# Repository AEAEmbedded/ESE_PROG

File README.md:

# ESE_PROG - Programming 5 / 6 (2026-2027)

Course repository for **Programming 5 (Prog 5)** and **Programming 6 (Prog 6)** of the
Embedded Systems Engineering track, Software Engineering, HAN University of Applied Sciences.

| Course | Period | When | Folder |
| --- | --- | --- | --- |
| **Prog 5** | Period 1 | September - October 2026 | [`Prog5/`](Prog5/) - lectures, labs, assignments, example code |
| **Prog 6** | Period 2 | November 2026 - January 2027 | [`Prog6/`](Prog6/) - workshops, Hackathon, Challenge, rubrics |

## Welcome to Prog 5

Prog 5 and Prog 6 are the final lap of the programming courses in your ESE journey. Together they
work towards one overall goal: **becoming a professional embedded software and systems developer**.

Prog 5 (period 1) is about object-oriented C++ on microcontrollers (Arduino / SAMD21) and on the
Raspberry Pi: writing sensor libraries, designing them with UML, connecting them to the outside
world (I2C, MQTT) and testing them. Prog 6 (period 2) builds on that with software-engineering
practice - build systems, unit testing, clean code and design patterns - and applies it in the
Hackathon and the Challenge project.

### Why everything is done with Git

All work in Prog 5 and 6 is done with **Git**, because it is the only way to reach our learning
goals. Git:

* lets several developers work on the same project at the same time;
* keeps a complete history of every change to the code;
* makes it easy to revert a change or recover an earlier version;
* helps you resolve conflicts between contributions efficiently.

More importantly, it takes you out of an artificial learning environment and into the professional
field: the companies where you will do your internship and, later, land a job use exactly these
tools. Being fluent in them is part of being a professional - see
[Coder vs Developer vs Software Engineer: what's the difference?](https://youtu.be/fcjBfSiyI0k)

### Handing in your work

Put your assignments in a (private) Git repository and add your lecturer as a collaborator
(GitHub username **jakorten**). Commit as you go - a
repository with a real history of small, meaningful commits is part of what is assessed.

## Prog 5 schedule and deadlines (period 1, 2026-2027)

The course starts on **Thursday 3 September 2026** and runs for seven weeks. Every week combines
one design principle, a C++ topic and a UML topic, and every Friday there is a lab. The first two
labs are Git and Requirements; from week 3 onwards the Friday lab is the next step of **one sensor
library** that grows week by week (the BME280 is the concrete sensor we use; another I2C sensor
works just as well). The same seven-step plan is on the schedule slide of every lecture deck.

| Week | Lecture (Thu) | Design principle | C++ | UML | Slides | Lab (Fri) |
| :-: | --- | --- | --- | --- | --- | --- |
| 1 | 3 Sep 2026 | Single Responsibility | Scope, namespaces, string | Use cases / class diagram | [0. Course introduction](Prog5/Keynotes/), [1. Introduction](Prog5/Keynotes/) | Fri 4 Sep: [Git workshop 1](Prog5/Workshops/Git/Workshop1_Basics.md) - the basics (clone, add, commit, push, .gitignore, handing in) |
| 2 | 10 Sep 2026 | Open-Closed Principle | Constructors, iterators, lambdas | Inheritance / generalization | [2. Constructors and more](Prog5/Keynotes/) | Fri 11 Sep: Requirements (SMART, FURPS+, MoSCoW, use cases) |
| 3 | 17 Sep 2026 | Liskov Substitution Principle | Lists, inline functions, default params | Activity diagrams | [3. Lists, inline functions and default params](Prog5/Keynotes/) | Fri 18 Sep: sensor library 1 - core, `Bus`, Arduino |
| 4 | 24 Sep 2026 | Interface Segregation Principle | Interfaces and abstract classes | Dependencies | [4. Interfaces and abstract classes](Prog5/Keynotes/) | Fri 25 Sep: sensor library 2 - Raspberry Pi, `Bus` / `Clock` split |
| 5 | 1 Oct 2026 | Dependency Inversion Principle | Threads, callbacks | Sequence diagrams | [5. Threading and callbacks](Prog5/Keynotes/) | Fri 2 Oct: sensor library 3 - sampler thread, callback, MQTT |
| 6 | 8 Oct 2026 | Coupling and cohesion | Polymorphism | Composition, packages | [6. Polymorphism](Prog5/Keynotes/) | Fri 9 Oct: sensor library 4 - polymorphism, UML design |
| 7 | 15 Oct 2026 | Embedded SOLID | Lifecycle: constructors, destructors, const | - | [7. Lifecycle](Prog5/Keynotes/) | Fri 16 Oct: sensor library 5 - RAII, host unit tests, refactor |

Each assignment is introduced in the lecture of the week listed below and is due **one week
later, on the Thursday of the following week**. Full hand-outs: [`Prog5/Assignments/`](Prog5/Assignments/).

| Week | Lecture | Assignment | Deadline |
| :-: | --- | --- | --- |
| 1 | Thu 3 Sep 2026 | **1.** Make a basic stepper motor library and hand it in via your Git repository. | Thu 10 Sep 2026 |
| 2 | Thu 10 Sep 2026 | **2.** Create a UML use-case diagram with description for a sensor application (e.g. KNMI / weather station). | Thu 17 Sep 2026 |
| 3 | Thu 17 Sep 2026 | **3.** [Sensor library, core + Arduino](Prog5/Assignments/week3/bme280_arduino_library.md): Bosch driver wrapped in a class, `Bus` interface, `ArduinoI2cBus`, example sketch. Tag `v0.3-arduino`. | Thu 24 Sep 2026 |
| 4 | Thu 24 Sep 2026 | **4.** [Same library on the Raspberry Pi](Prog5/Assignments/week4/bme280_raspberry_pi.md): CMake build, `LinuxI2cBus`, `Bus` / `Clock` split (ISP), dependency diagram. Tag `v0.4-pi`. | Thu 1 Oct 2026 |
| 5 | Thu 1 Oct 2026 | **5.** [Sampling thread, callback, MQTT](Prog5/Assignments/week5/bme280_mqtt.md): `Sampler`, `Publisher` / `MqttPublisher`, `EnvironmentSensor` + `FakeSensor`, sequence diagram sketch. Tag `v0.5-mqtt`. | Thu 8 Oct 2026 |
| 6 | Thu 8 Oct 2026 | **6.** [Design on paper](Prog5/Assignments/week6/bme280_uml_design.md): class, package and sequence diagrams of the library; `vector<EnvironmentSensor*>` with a second sensor. Tag `v0.6-design`. | Thu 15 Oct 2026 |
| 7 | Thu 15 Oct 2026 | **7.** [Unit tests on the host](Prog5/Assignments/week7/bme280_tests_and_refactor.md) with the `MockBus` (no mocking framework yet). <br> **8.** Review the library against DRY, KISS, SOLID, coupling / cohesion and the lifecycle checklist; add a second sensor and move the shared abstractions (`Bus`, `Clock`, `EnvironmentSensor`) into their own package; refactor and report. Tag `v1.0`. | Thu 22 Oct 2026 |

**Resit:** assignments that were not handed in on time, or that did not pass, can be (re)submitted
until the resit deadline of **Thursday 29 October 2026**.

Assignments 3-8 all build on the same sensor library (the Friday labs are its steps), so keep it in one repository and let its
history show how it grows: from a first Arduino version to a tested, refactored Pi library that
publishes over MQTT. Starter code per week is in [`Prog5/Code/`](Prog5/Code/) (`week2`: the
wrapper library, `week4`: Linux I2C bus, `week5`: sampler + MQTT).

## Learning outcomes

The learning outcomes below follow the HAN engineering competencies used in the rubrics
(*Analyze - Design - Manage - Control - Realize - Professionalize*). Prog 5 lays the foundation;
Prog 6 raises every outcome to a professional level and assesses it in the Hackathon and the
Challenge.

### Prog 5 - after period 1 you can

| # | Learning outcome | Competency |
| :-: | --- | --- |
| P5.1 | **Analyse** a realistic problem into user stories and SMART requirements, categorised with FURPS+ and prioritised with MoSCoW. | Analyze |
| P5.2 | **Design** software with UML: a use-case diagram with descriptions, a class diagram and a sequence diagram (and a state diagram where behaviour asks for it). | Design |
| P5.3 | **Implement** object-oriented C++ on embedded targets (Arduino / SAMD21 and Raspberry Pi): classes and encapsulation, constructors/destructors and object lifecycle, inheritance, abstract classes and interfaces, polymorphism, smart pointers, lambdas and callbacks, basic concurrency. | Realize |
| P5.4 | **Build reusable sensor libraries**: an Arduino library for an (I2C) sensor, a C++ library for an I2C sensor on the Raspberry Pi, and connect it to an MQTT broker. | Realize |
| P5.5 | **Apply DRY, KISS, SOLID and loose coupling / strong cohesion**, recognise where your own code violates them, refactor it and explain what improved. | Realize |
| P5.6 | **Test** a library with basic unit tests in C++. | Control |
| P5.7 | **Use Git professionally** for all your work: meaningful commits, branches, pull requests and a readable history, in a repository you share with your lecturer. | Manage |

### Prog 6 - after period 2 you can

| # | Learning outcome | Competency |
| :-: | --- | --- |
| P6.1 | **Set up and maintain a CMake build** for a C/C++ project with its own libraries and externally fetched test dependencies, and explain why build systems exist. | Realize |
| P6.2 | **Unit test at a professional level** with CppUTest, including test doubles and mocks for hardware dependencies, and position tests in the testing pyramid. | Control |
| P6.3 | **Write clean, well-commented, maintainable code**: recognise code smells, apply MISRA C++:2023 guidelines and use static-analysis tooling to check your own code. | Realize |
| P6.4 | **Apply embedded design patterns and architecture** (state, observer, hardware proxy, cyclic executive, debouncing, fixed-point arithmetic, humble object) with awareness of their run-time and memory overhead. | Design |
| P6.5 | **Realise a working proof-of-concept** for a healthcare case (Wilhelmina Children's Hospital, WKZ) - in a team under time pressure in the Hackathon and in the longer Challenge project - from analysis and SOLID design, through technical designs (class, sequence, state), to a tested implementation. | Analyze / Design / Realize |
| P6.6 | **Manage code as a team** in Git with commits, pull requests, blame and code reviews throughout the project. | Manage |
| P6.7 | **Reflect and advise**: give substantiated advice based on your analysis and proof-of-concept and present it convincingly (presentation, report or video), communicating professionally with the team, lecturers and domain experts. | Professionalize |

Assessment: Prog 5 by the weekly assignments (see schedule below); Prog 6 with the
[Hackathon and Prog 6 rubrics](Prog6/Rubrics/).

## Repository layout

| Folder | Contents |
| --- | --- |
| [`Prog5/Keynotes/`](Prog5/Keynotes/) | Lecture slides (PDF): course introduction and lectures 1-7. |
| [`Prog5/Labs/`](Prog5/Labs/) | Lab hand-outs (Lab 2: Arduino basics with OOP / SOLID; Lab 3: I2C sensor library). |
| [`Prog5/Assignments/`](Prog5/Assignments/) | Assignment hand-outs per week; from week 3 on all steps of the one sensor library (BME280 as the worked example). |
| [`Prog5/Code/week1/`](Prog5/Code/week1/) | Week 1 example code: stepper motor examples, `SimpleStepper` library, TB6600 test. |
| [`Prog5/Code/week2/`](Prog5/Code/week2/) | BME280 starter library: `Bus` interface, wrapper around the vendored Bosch BME280 SensorAPI, `MockBus` + doctest. |
| [`Prog5/Code/week4/`](Prog5/Code/week4/) | `rpi_platform`: `LinuxI2cBus` on `/dev/i2c-1` and a smoke test, CMake build of core + platform. |
| [`Prog5/Code/week5/`](Prog5/Code/week5/) | `mqtt_station`: `EnvironmentSensor`, `Sampler` (thread + callback), `Publisher` / `MqttPublisher` (libmosquitto), composition root. |
| [`Prog5/Code/Examples/`](Prog5/Code/Examples/) | Demo code used in the lectures and labs (abstract interfaces, object lifecycle, ToF sensor library, SOLID terminal, I2C scanner). |
| [`Prog5/Workshops/Git/`](Prog5/Workshops/Git/) | Git workshops 1 (the basics) and 2 (working together), with an interactive version. |
| [`Prog5/Demos/`](Prog5/Demos/) | Hand-outs: Git manual, CMake basics, interfaces demo. |
| [`Prog6/Workshops/`](Prog6/Workshops/) | Workshops: CMake, Unit Testing (CppUTest), Commenting, Clean Code / MISRA C++, Design Patterns & Architecture. |
| [`Prog6/Hackathon/`](Prog6/Hackathon/) | Hackathon material: the VitalSignsBox modules (ECG lead detection, SpO2 detection, temperature sensors) with firmware, API descriptions and hardware files. |
| [`Prog6/Challenge/`](Prog6/Challenge/) | Challenge project: assignment document and hardware design files (SensorHub, ActuatorHub, sim modules, adapters). |
| [`Prog6/Rubrics/`](Prog6/Rubrics/) | Assessment rubrics 2026-2027 (Prog 6 v1.5, Hackathon v1.4; Markdown source + PDF) and previous editions. |
| [`Resources/`](Resources/) | Background reading, e.g. choosing a development method. |

## How to use

1. Clone the repository: `git clone https://github.com/AEAEmbedded/ESE_PROG`
2. Arduino sketches (`*.ino`): open the sketch folder in the Arduino IDE and upload to your board.
3. CMake projects (workshops): configure out-of-source, e.g.
   ```bash
   cmake -S Prog6/Workshops/UnitTesting/Source/TemperatureTestFinished -B build
   cmake --build build
   ctest --test-dir build
   ```
   Build directories are ignored by git - do not commit them.
4. Refer to the keynotes, labs and workshop READMEs for instructions.

## Related repositories

* **[PiTest](https://github.com/jakorten/PiTest)** - Raspberry Pi 4 to SensorHub (SAMD21) I2C communication test (Python for the Pi, C++ Arduino sketches for the SAMD21).

## Disclaimer

This repository is for educational purposes. The code may be incomplete or contain errors. Use at your own risk.

## Contact

Johan Korten - johan.korten@han.nl

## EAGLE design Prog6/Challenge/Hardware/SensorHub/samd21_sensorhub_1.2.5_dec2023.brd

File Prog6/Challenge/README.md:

# Challenge

This folder contains resources for the Prog6 Challenge project.

## Repositories

- **[PiTest](https://github.com/jakorten/PiTest)** - Raspberry Pi 4 to SensorHub (SAMD21) I2C communication test
 - Python I2C test script for Pi
 - C++ Arduino sketch for SAMD21
 - Pinout documentation

## Contents

- **HAN_Challenge_Prog_6_2025.pdf** - Challenge assignment document (2025 edition; to be updated for 2026-2027)
- **Hardware/** - Hardware design files and schematics

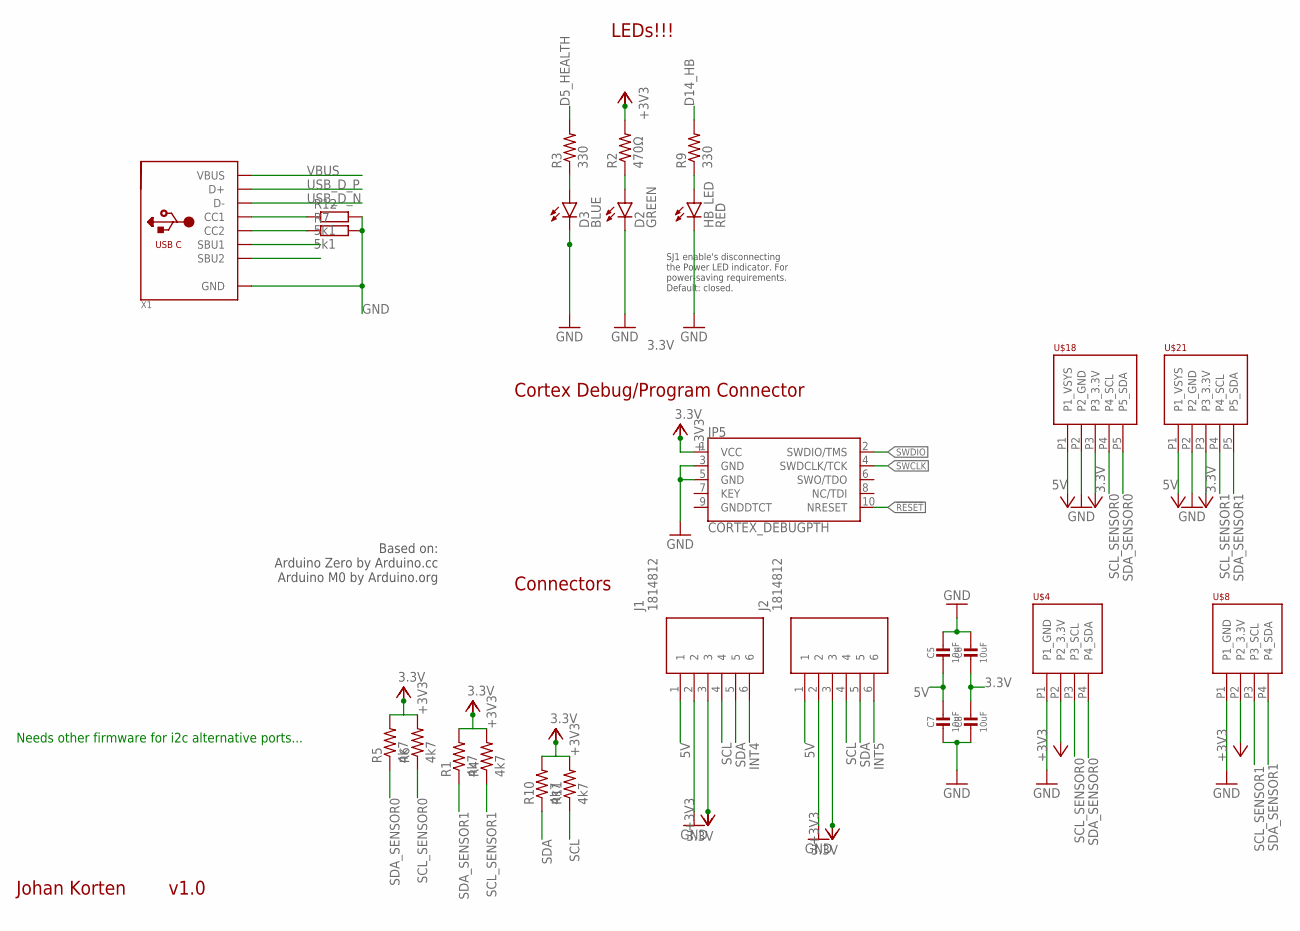
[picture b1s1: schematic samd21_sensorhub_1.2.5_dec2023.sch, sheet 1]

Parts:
C5, C6, C7, C8: 10uF; 0805-NO
D2: GREEN; LED-0603
D3: BLUE; LED-0603
HB_LED: RED; LED-0603
J1, J2: 1814812
JP5: CORTEX_DEBUGPTH; 2X5-PTH-1.27MM
R1, R4, R5, R6, R10, R11: 4k7; 0603-RES
R2: 470Ω; 0603-RES
R3, R9: 330; 0603-RES
R7, R12: 5k1; R0603
U$4, U$8: PHOENIX_PTSM_M4_THANGLE; PTSM_M4_TH
U$18, U$21: PHOENIX_PTSM_M5_TH_I2C++; PTSM_M5_THRHOLE
X1: USB_C; USB_C_CUSB31-CFM2AX-01-X

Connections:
3.3V: C6.2, C8.1, J1.3, J2.3, JP5.1 (VCC), R1.2, R2.2, R4.2, R5.2, R6.2, R10.2, R11.2, U$4.P2 (P2_3.3V), U$8.P2 (P2_3.3V), U$18.P3 (P3_3.3V), U$21.P3 (P3_3.3V); also elsewhere on the board
5V: C5.2, C7.1, J1.1, J2.1, U$18.P1 (P1_VSYS), U$21.P1 (P1_VSYS); also elsewhere on the board
!RESET: JP5.10 (NRESET); also elsewhere on the board
D5_HEALTH: R3.2; also elsewhere on the board
D5_HEALTH_LED: D3.A, R3.1
D14_HB: R9.2; also elsewhere on the board
D14_HB_LED: HB_LED.A, R9.1
GND: C5.1, C6.1, C7.2, C8.2, D2.C, D3.C, HB_LED.C, J1.2, J2.2, JP5.3 (GND), JP5.5 (GND), R7.2, R12.2, U$4.P1 (P1_GND), U$8.P1 (P1_GND), U$18.P2 (P2_GND), U$21.P2 (P2_GND), X1.A1B12 (GND), X1.B1A12 (GND); also elsewhere on the board
INT4: J1.6; also elsewhere on the board
INT5: J2.6; also elsewhere on the board
unnamed: R12.1, X1.A5 (CC1)
unnamed: R7.1, X1.B5 (CC2)
unnamed: D2.A, R2.1
SCL: J1.4, J2.4, R11.1; also elsewhere on the board
SCL_SENSOR0: R6.1, U$4.P3 (P3_SCL), U$18.P4 (P4_SCL); also elsewhere on the board
SCL_SENSOR1: R4.1, U$8.P3 (P3_SCL), U$21.P4 (P4_SCL); also elsewhere on the board
SDA: J1.5, J2.5, R10.1; also elsewhere on the board
SDA_SENSOR0: R5.1, U$4.P4 (P4_SDA), U$18.P5 (P5_SDA); also elsewhere on the board
SDA_SENSOR1: R1.1, U$8.P4 (P4_SDA), U$21.P5 (P5_SDA); also elsewhere on the board
SWCLK: JP5.4 (SWDCLK/TCK); also elsewhere on the board
SWDIO: JP5.2 (SWDIO/TMS); also elsewhere on the board
USB_D_N: X1.A7 (D-), X1.B7 (D-); also elsewhere on the board
USB_D_P: X1.A6 (D+), X1.B6 (D+); also elsewhere on the board
VBUS: X1.A4B9 (VBUS), X1.B4A9 (VBUS); also elsewhere on the board

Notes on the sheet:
LEDs!!!
Cortex Debug/Program Connector
Connectors
Johan Korten
v1.0
SJ1 enable's disconnecting the Power LED indicator. For power-saving requirements. Default: closed.
Based on: Arduino Zero by Arduino.cc Arduino M0 by Arduino.org
Needs other firmware for i2c alternative ports...

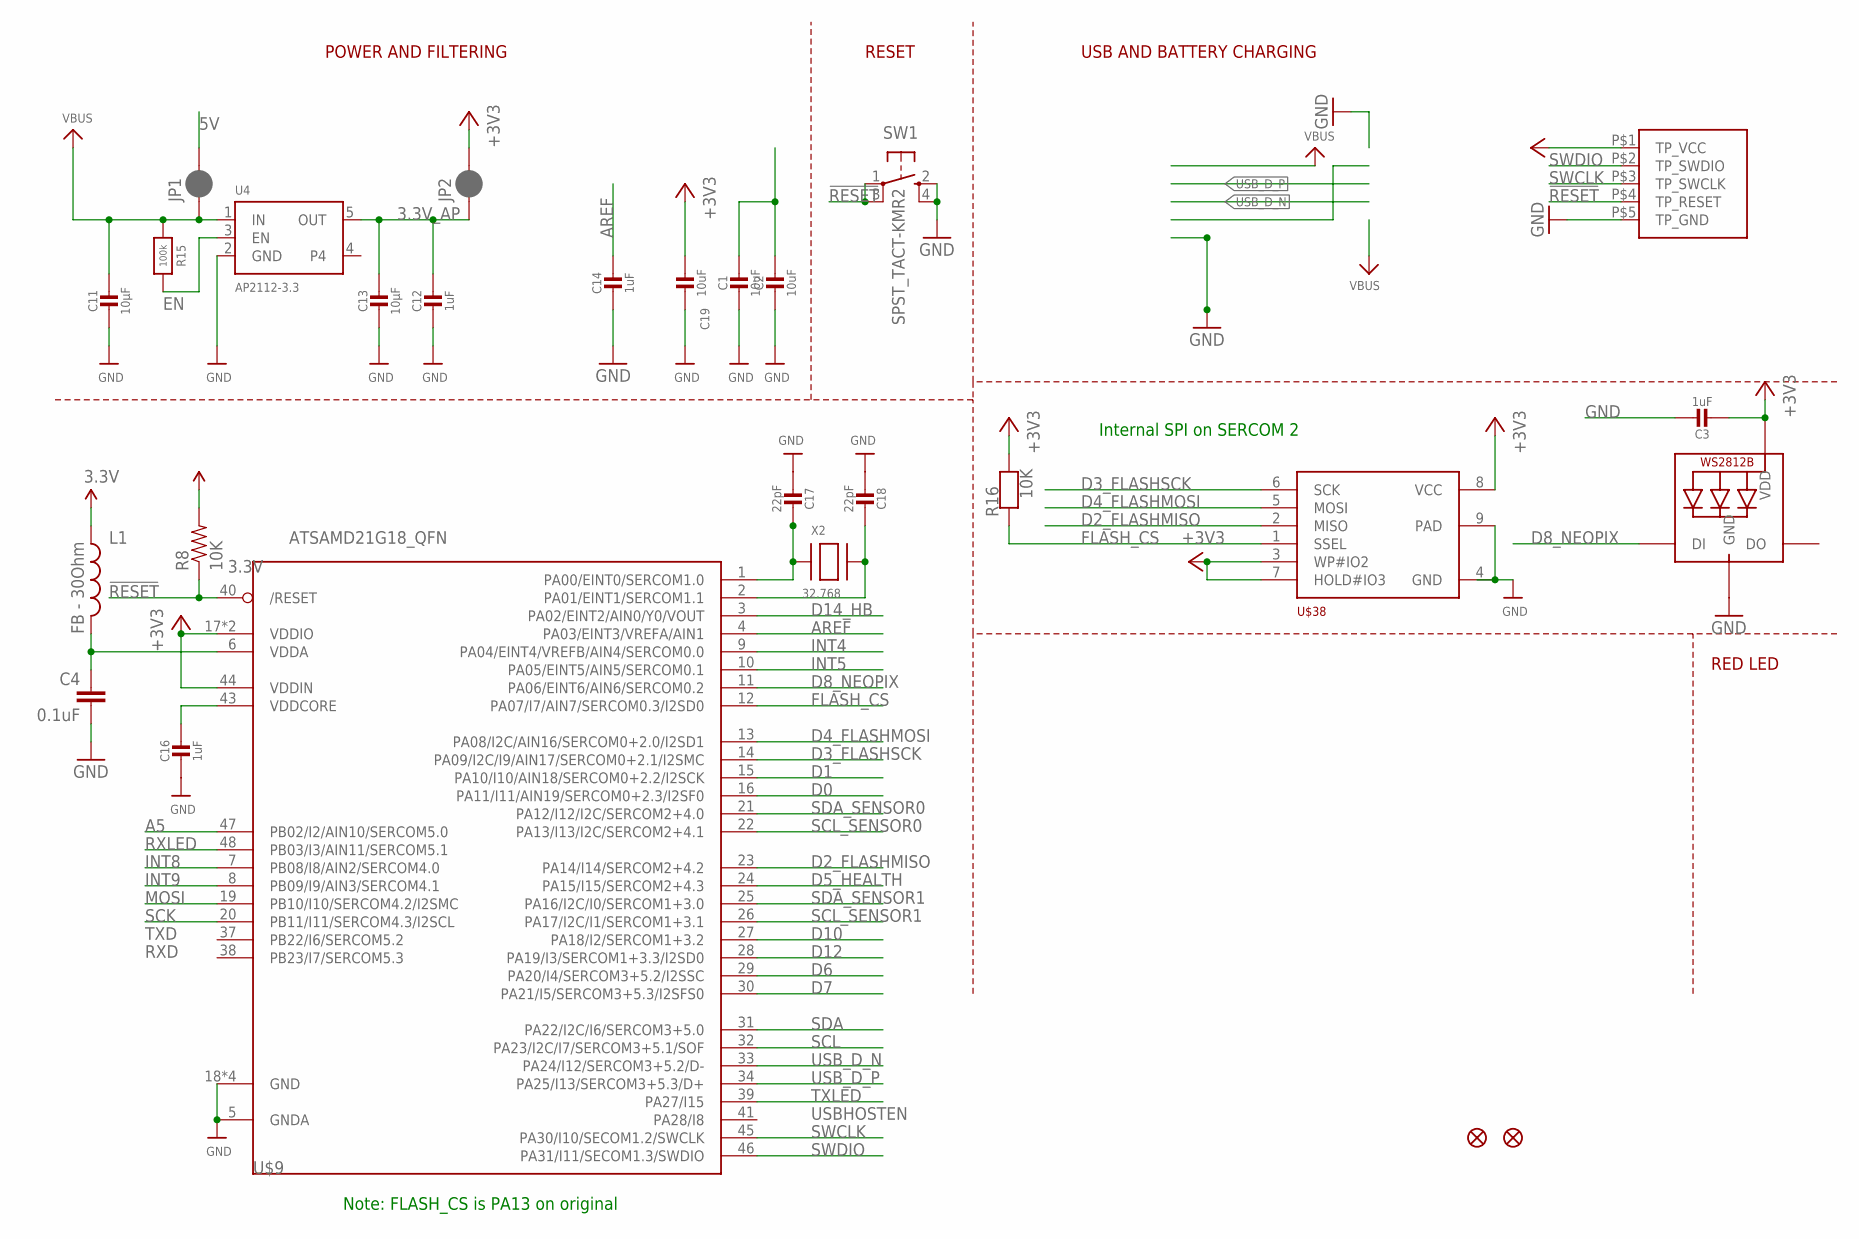
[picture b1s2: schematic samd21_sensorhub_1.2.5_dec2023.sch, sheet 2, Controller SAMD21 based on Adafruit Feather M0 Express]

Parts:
C1, C2, C19: 10uF; 0805-NO
C3, C12, C14, C16: 1uF; 0603-NO
C4: 0.1uF; 0402-CAP
C11, C13: 10µF; 0805-NO
C17, C18: 22pF; 0603-NO
JP1, JP2: JUMPER-SMT_2_NC_PASTE_SILK; SMT-JUMPER_2_NC_PASTE_SILK
L1: FB - 30Ohm; 0603
LED1: WS2812B3535; LED3535
R8: 10K; 0603-RES
R15: 100k; 0603-NO
R16: 10K; 0603-NO
SW1: SPST_TACT-KMR2; KMR2
U4: AP2112-3.3; SOT23-5
U$5: HUB_TESTPINSHUBS; TEST_PINS
U$9: ATSAMD21G18_QFN; TQFN48_7MM
U$34, U$35: FIDUCIAL""; FIDUCIAL_1MM
U$38: S25FL064LABNFI040; SON80P400X400X60-9N
X2: 32.768; XTAL3215

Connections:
3.3V: C3.2, C19.1, JP2.2, L1.1, LED1.2 (VDD), R8.2, R16.2, U$5.P$1 (TP_VCC), U$9.17 (VDDIO), U$9.36 (VDDIO), U$9.44 (VDDIN), U$38.3 (WP#IO2), U$38.7 (HOLD#IO3), U$38.8 (VCC); also elsewhere on the board
3.3V_AP: C12.1, C13.1, JP2.1, U4.5 (OUT)
5V: C1.1, C2.1, JP1.2; also elsewhere on the board
!RESET: R8.1, SW1.1, SW1.3 (P1), U$5.P$4 (TP_RESET), U$9.40 (/RESET); also elsewhere on the board
A5: U$9.47 (PB02/I2/AIN10/SERCOM5.0)
AREF: C14.1, U$9.4 (PA03/EINT3/VREFA/AIN1)
D0: U$9.16 (PA11/I11/AIN19/SERCOM0+2.3/I2SF0)
D1: U$9.15 (PA10/I10/AIN18/SERCOM0+2.2/I2SCK)
D2_FLASHMISO: U$9.23 (PA14/I14/SERCOM2+4.2), U$38.2 (MISO)
D3_FLASHSCK: U$9.14 (PA09/I2C/I9/AIN17/SERCOM0+2.1/I2SMC), U$38.6 (SCK)
D4_FLASHMOSI: U$9.13 (PA08/I2C/AIN16/SERCOM0+2.0/I2SD1), U$38.5 (MOSI)
D5_HEALTH: U$9.24 (PA15/I15/SERCOM2+4.3); also elsewhere on the board
D6: U$9.29 (PA20/I4/SERCOM3+5.2/I2SSC)
D7: U$9.30 (PA21/I5/SERCOM3+5.3/I2SFS0)
D8_NEOPIX: LED1.1 (DI), U$9.11 (PA06/EINT6/AIN6/SERCOM0.2)
D10: U$9.27 (PA18/I2/SERCOM1+3.2)
D12: U$9.28 (PA19/I3/SERCOM1+3.3/I2SD0)
D14_HB: U$9.3 (PA02/EINT2/AIN0/Y0/VOUT); also elsewhere on the board
EN: R15.2, U4.3 (EN)
FLASH_CS: R16.1, U$9.12 (PA07/I7/AIN7/SERCOM0.3/I2SD0), U$38.1 (SSEL)
GND: C1.2, C2.2, C3.1, C4.2, C11.2, C12.2, C13.2, C14.2, C16.2, C17.2, C18.2, C19.2, LED1.4 (GND), SW1.2 (S), SW1.4 (S1), U4.2 (GND), U$5.P$5 (TP_GND), U$9.5 (GNDA), U$9.18 (GND), U$9.35 (GND), U$9.42 (GND), U$9.THERMAL (GND), U$38.4 (GND), U$38.9 (PAD); also elsewhere on the board
INT4: U$9.9 (PA04/EINT4/VREFB/AIN4/SERCOM0.0); also elsewhere on the board
INT5: U$9.10 (PA05/EINT5/AIN5/SERCOM0.1); also elsewhere on the board
INT8: U$9.7 (PB08/I8/AIN2/SERCOM4.0)
INT9: U$9.8 (PB09/I9/AIN3/SERCOM4.1)
MOSI: U$9.19 (PB10/I10/SERCOM4.2/I2SMC)
unnamed: C17.1, U$9.1 (PA00/EINT0/SERCOM1.0), X2.P$1
unnamed: C18.1, U$9.2 (PA01/EINT1/SERCOM1.1), X2.P$2
RXLED: U$9.48 (PB03/I3/AIN11/SERCOM5.1)
SCK: U$9.20 (PB11/I11/SERCOM4.3/I2SCL)
SCL: U$9.32 (PA23/I2C/I7/SERCOM3+5.1/SOF); also elsewhere on the board
SCL_SENSOR0: U$9.22 (PA13/I13/I2C/SERCOM2+4.1); also elsewhere on the board
SCL_SENSOR1: U$9.26 (PA17/I2C/I1/SERCOM1+3.1); also elsewhere on the board
SDA: U$9.31 (PA22/I2C/I6/SERCOM3+5.0); also elsewhere on the board
SDA_SENSOR0: U$9.21 (PA12/I12/I2C/SERCOM2+4.0); also elsewhere on the board
SDA_SENSOR1: U$9.25 (PA16/I2C/I0/SERCOM1+3.0); also elsewhere on the board
SWCLK: U$5.P$3 (TP_SWCLK), U$9.45 (PA30/I10/SECOM1.2/SWCLK); also elsewhere on the board
SWDIO: U$5.P$2 (TP_SWDIO), U$9.46 (PA31/I11/SECOM1.3/SWDIO); also elsewhere on the board
TXLED: U$9.39 (PA27/I15)
USB_D_N: U$9.33 (PA24/I12/SERCOM3+5.2/D-); also elsewhere on the board
USB_D_P: U$9.34 (PA25/I13/SERCOM3+5.3/D+); also elsewhere on the board
VBUS: C11.1, JP1.1, R15.1, U4.1 (IN); also elsewhere on the board
VDDANA: C4.1, L1.2, U$9.6 (VDDA)
VDDCORE1: C16.1, U$9.43 (VDDCORE)

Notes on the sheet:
POWER AND FILTERING
RESET
USBHOSTEN
TXD
RXD
USB AND BATTERY CHARGING
RED LED
Internal SPI on SERCOM 2
Note: FLASH_CS is PA13 on original

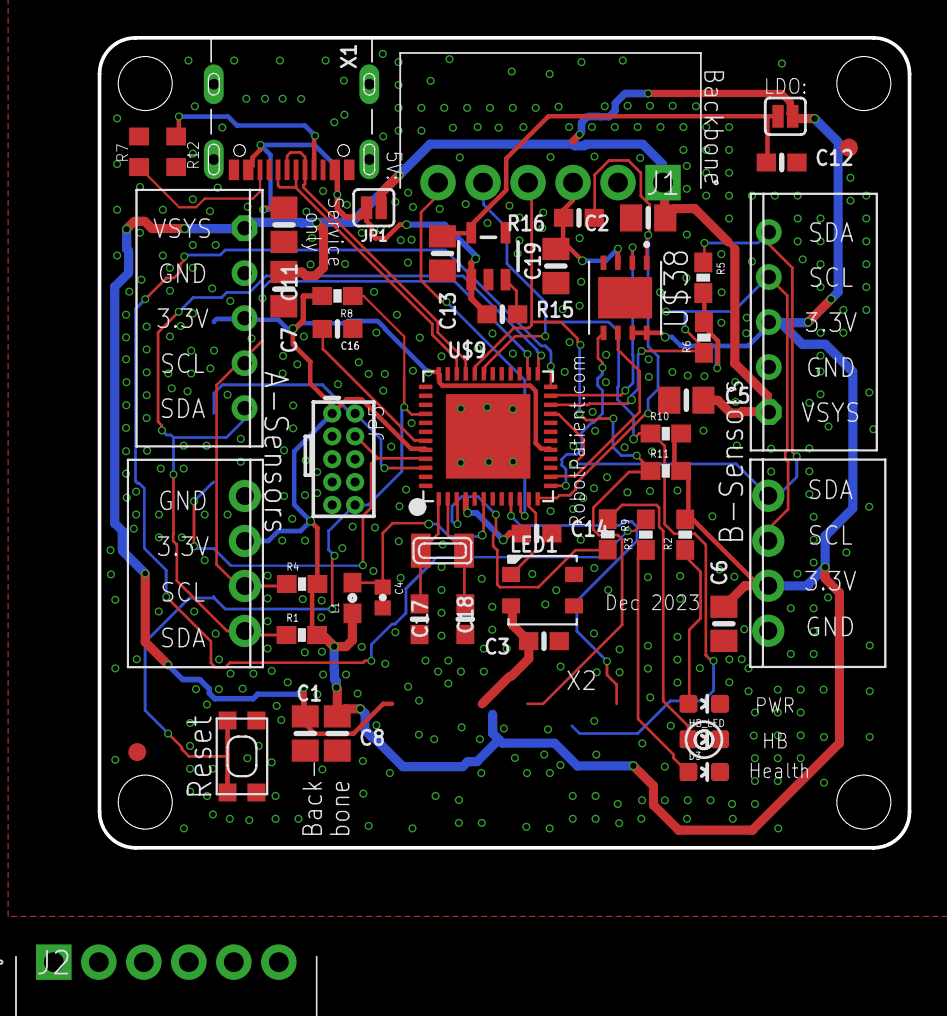
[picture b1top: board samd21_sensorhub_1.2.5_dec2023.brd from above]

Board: 2 copper layers, 45.0 x 45.0 mm, 53 parts (0 on the bottom side), 36 nets.

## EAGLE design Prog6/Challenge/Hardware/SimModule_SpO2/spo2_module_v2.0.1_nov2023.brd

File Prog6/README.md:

# Prog 6 - period 2 (November 2026 - January 2027)

Software-engineering practice for embedded systems, applied in two projects: the **Hackathon**
(short, in teams, on the VitalSignsBox hardware) and the **Challenge** (longer project on the
SensorHub / ActuatorHub platform). Both are assessed with the rubrics in [`Rubrics/`](Rubrics/).
Learning outcomes are in the [main README](../README.md#learning-outcomes).

| Folder | Contents |
| --- | --- |
| [`Workshops/`](Workshops/) | Five workshops with slides and source: CMake, Unit Testing (CppUTest), Commenting, Clean Code / MISRA C++:2023, Design Patterns & Architecture. See [`Workshops/README.md`](Workshops/README.md). |
| [`Hackathon/`](Hackathon/) | [VitalSignsBox](Hackathon/VitalSignsBox/): ECG lead detection, SpO2 detection and temperature-sensor modules - firmware, I2C API descriptions and hardware files. |
| [`Challenge/`](Challenge/) | Challenge assignment document and hardware design files (SensorHub, ActuatorHub, sim modules for ECG / NIBP / SpO2 / temperature, adapters). |
| [`Rubrics/`](Rubrics/) | 2026-2027 rubrics: Prog 6 v1.5 and Hackathon v1.4 (Markdown source + PDF), plus previous editions in `Legacy/`. |

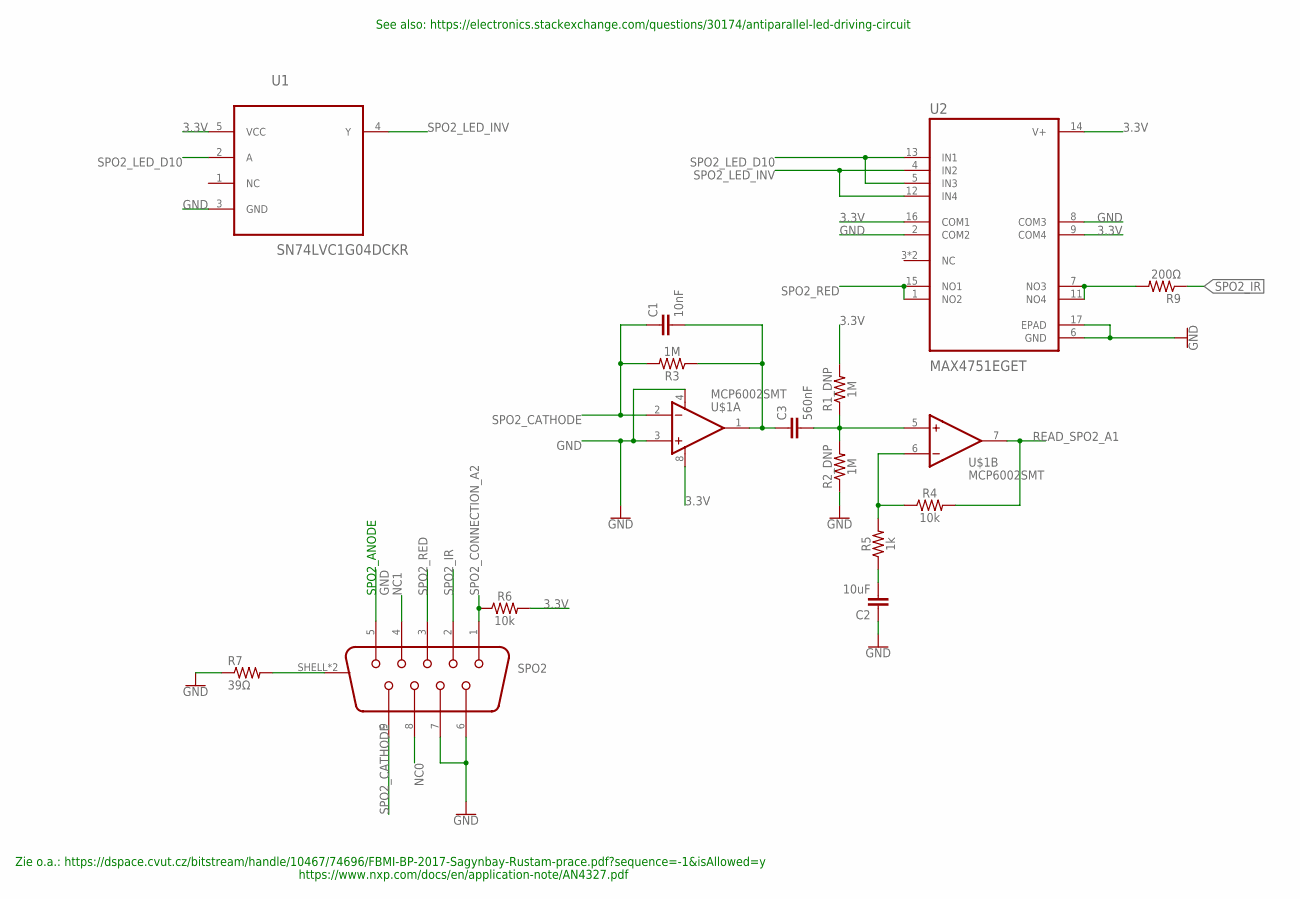
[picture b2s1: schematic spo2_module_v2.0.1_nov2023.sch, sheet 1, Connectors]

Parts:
C1: 10nF; 0603
C2: 10uF; C0603
C3: 560nF; C0603
R1_DNP, R2_DNP, R3: 1M; 0603
R4, R6: 10k; 0603
R5: 1k; 0603
R7: 39Ω; R0603
R9: 200Ω; R0603
SPO2: 618009231121
U1: SN74LVC1G04DCKR; SOT65P210X110-5N
U2: MAX4751EGET; QFN50P300X300X90-17N
U$1: MCP6002SMT; SOIC8

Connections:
3.3V: R1_DNP.2, R6.2, U1.5 (VCC), U2.9 (COM4), U2.14 (V+), U2.16 (COM1), U$1.8 (V+); also elsewhere on the board
GND: C2.1, R2_DNP.1, R7.1, SPO2.5, SPO2.6, SPO2.7, U1.3 (GND), U2.2 (COM2), U2.6 (GND), U2.8 (COM3), U2.17 (EPAD), U$1.3 (+IN), U$1.4 (V-); also elsewhere on the board
unnamed: C3.2, R1_DNP.1, R2_DNP.2, U$1.5 (+IN)
unnamed: C1.2, C3.1, R3.1, U$1.1 (OUT)
unnamed: R7.2, SPO2.SHELL (SHIELD), SPO2.SHELL1 (SHIELD)
unnamed: R4.1, R5.2, U$1.6 (-IN)
unnamed: R9.2, U2.7 (NO3), U2.11 (NO4)
unnamed: C2.2, R5.1
NC0: SPO2.8
NC1: SPO2.4
READ_SPO2_A1: R4.2, U$1.7 (OUT); also elsewhere on the board
SPO2_CATHODE: C1.1, R3.2, SPO2.9, U$1.2 (-IN)
SPO2_CONNECTION_A2: R6.1, SPO2.1; also elsewhere on the board
SPO2_IR: R9.1, SPO2.2
SPO2_LED_D10: U1.2 (A), U2.5 (IN3), U2.13 (IN1); also elsewhere on the board
SPO2_LED_INV: U1.4 (Y), U2.4 (IN2), U2.12 (IN4)
SPO2_RED: SPO2.3, U2.1 (NO2), U2.15 (NO1)

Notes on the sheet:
Zie o.a.: https://dspace.cvut.cz/bitstream/handle/10467/74696/FBMI-BP-2017-Sagynbay-Rustam-prace.pdf?sequence=-1&isAllowed=y
SPO2_ANODE
https://www.nxp.com/docs/en/application-note/AN4327.pdf
See also: https://electronics.stackexchange.com/questions/30174/antiparallel-led-driving-circuit

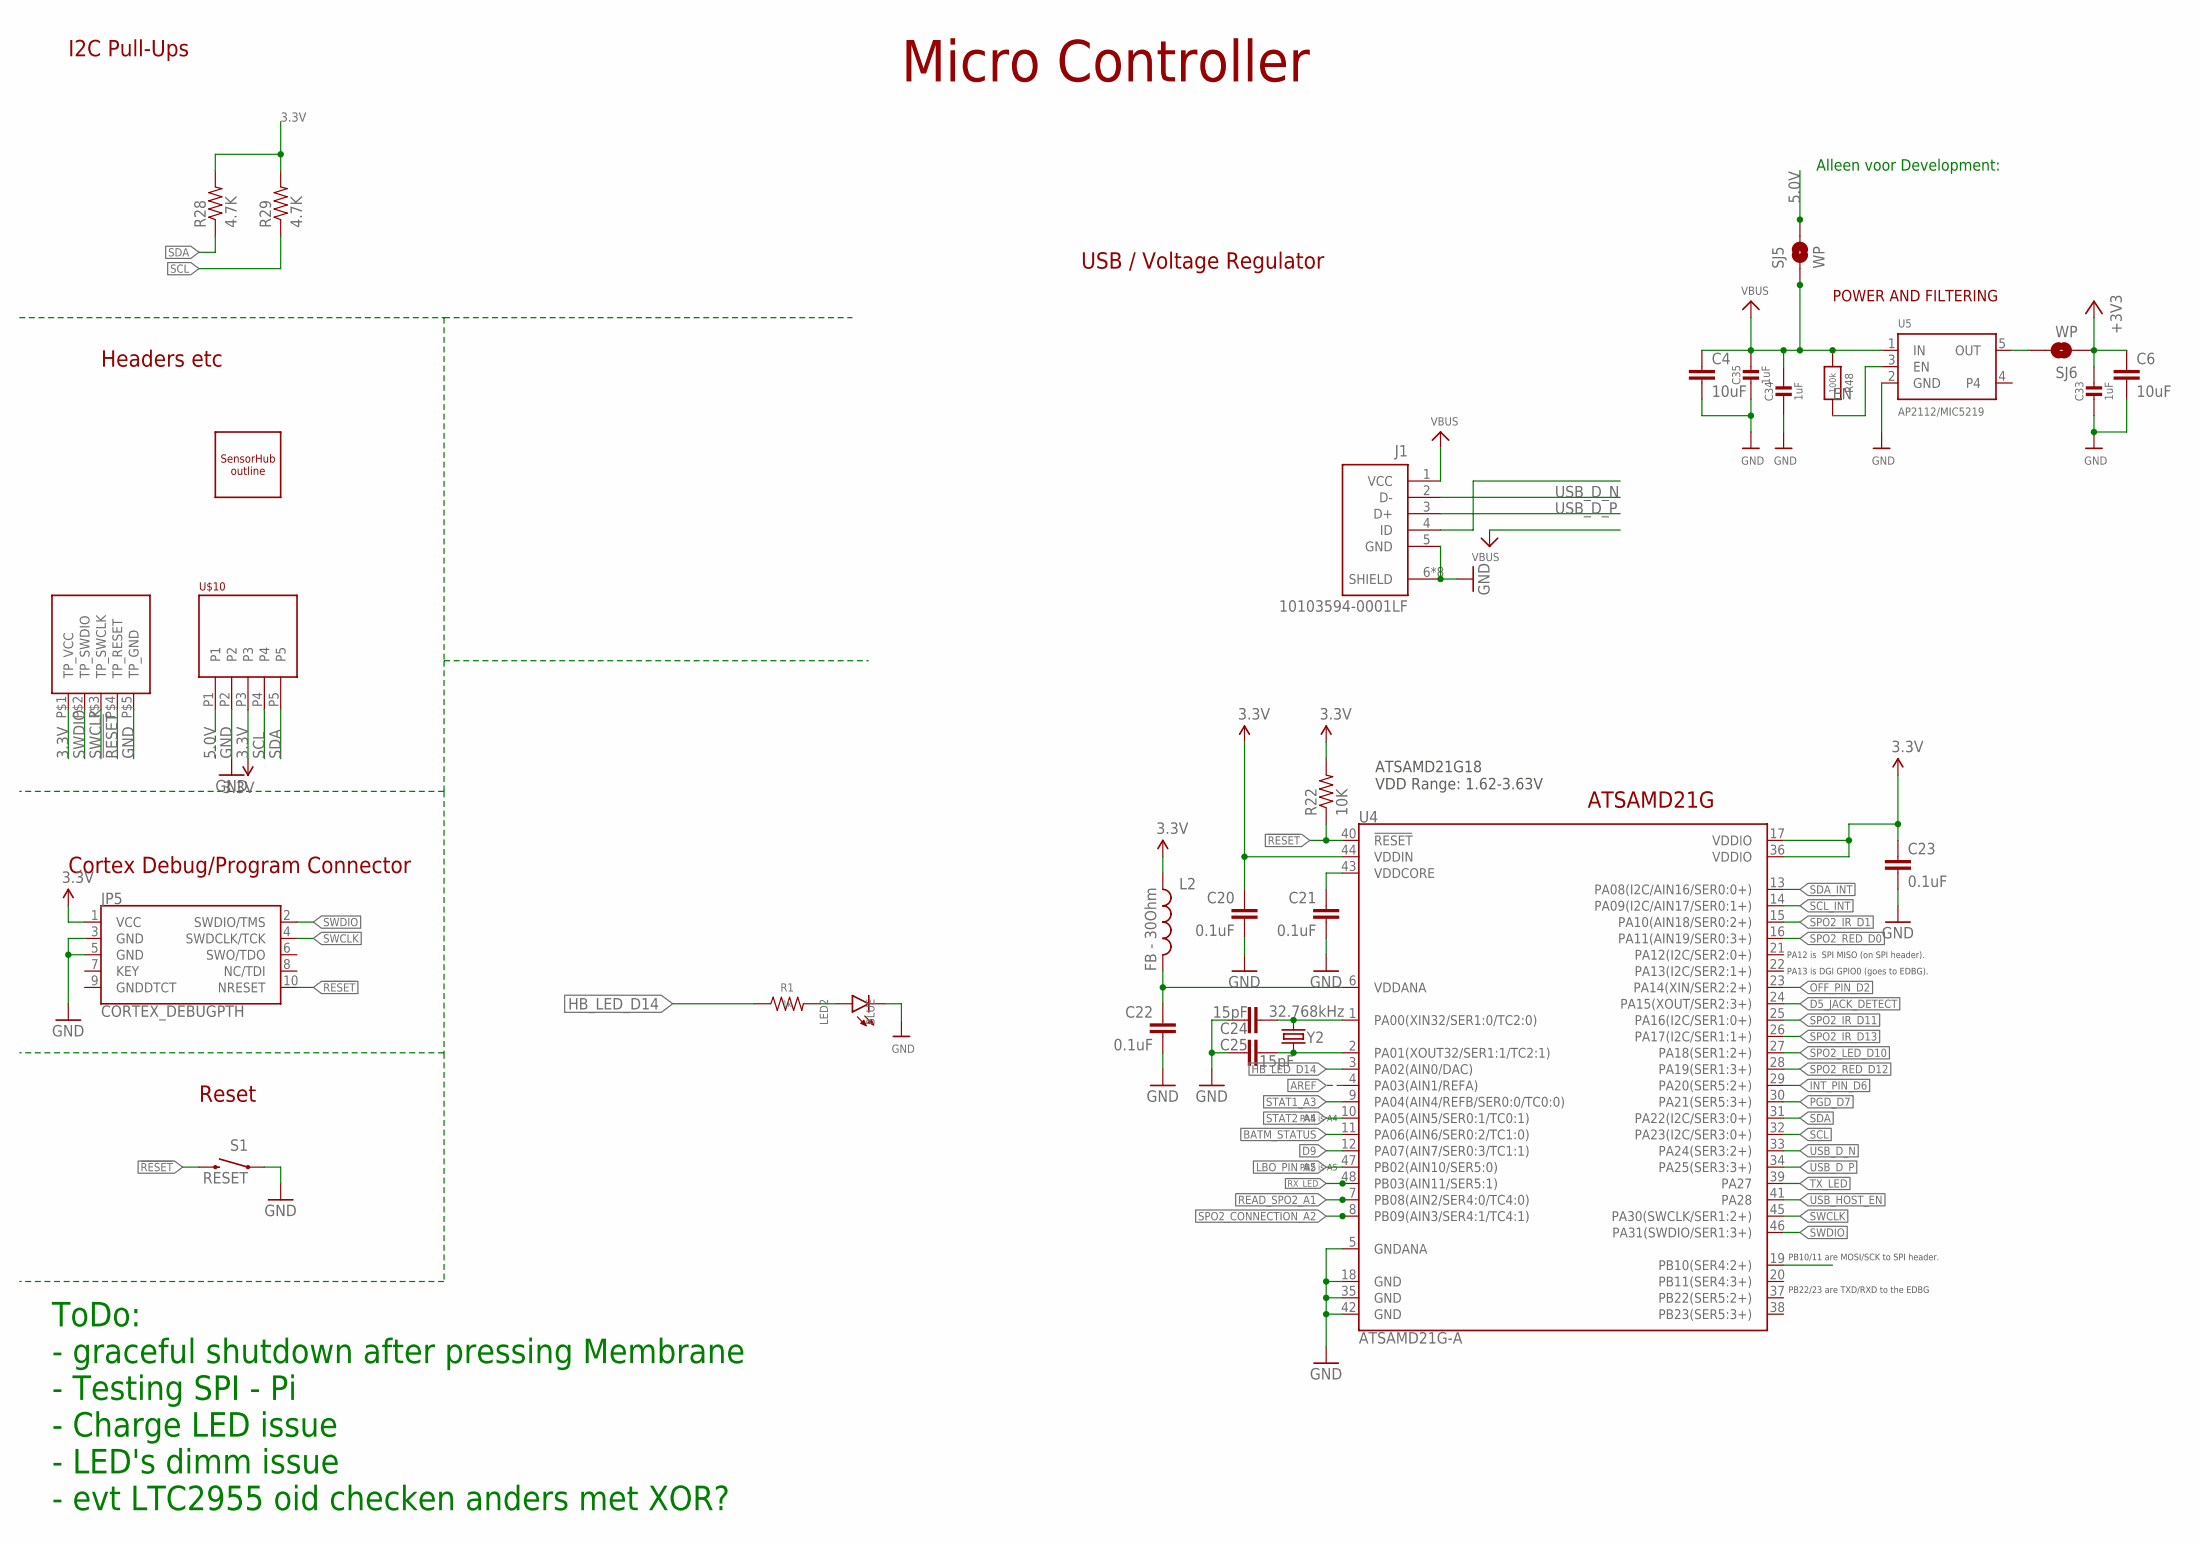
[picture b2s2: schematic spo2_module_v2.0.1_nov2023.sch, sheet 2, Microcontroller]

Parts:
C4, C6: 10uF; 0603
C20, C22, C23: 0.1uF; 0402-CAP
C21: 0.1uF; 0603
C24, C25: 15pF; 0402-CAP
C33, C34, C35: 1uF; 0603-NO
J1: 10103594-0001LF; AMPHENOL_10103594-0001LF
JP5: CORTEX_DEBUGPTH; 2X5-PTH-1.27MM
L2: FB - 30Ohm; 0603
LED2: BLUE; CHIP-LED0603
R1: 1k; 0603
R22: 10K; 0603-RES
R28, R29: 4.7K; 0603-RES
R48: 100k; 0603-NO@1
S1: RESET; TACTILE_SWITCH_SMD_4.6X2.8MM
SJ5, SJ6: WP; SMT-JUMPER_2_NO_NO-SILK
U4: ATSAMD21G-A; TQFP-48
U5: AP2112/MIC5219; SOT23-5
U$5: HUB_TESTPINSHUBS; TEST_PINS
U$10: PHOENIX_PTSM_M5_TH_I2C++; PTSM_M5_THRHOLE
U$12: SENSORHUB_PROFILEUSB_LEFT; SENSORHUB_OUTLINE_USB_NOTCH_LEFT
Y2: 32.768kHz; CRYSTAL-SMD-3.2X1.5MM

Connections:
3.3V: C6.1, C20.1, C23.1, C33.1, JP5.1 (VCC), L2.1, R22.2, R28.2, R29.2, SJ6.1, U4.17 (VDDIO), U4.36 (VDDIO), U4.44 (VDDIN), U$5.P$1 (TP_VCC), U$10.P3; also elsewhere on the board
5.0V: SJ5.2, U$10.P1
!RESET: JP5.10 (NRESET), R22.1, S1.3 (2), S1.4 (2), U4.40 (!RESET!), U$5.P$4 (TP_RESET)
AREF: U4.4 (PA03(AIN1/REFA))
BATM_STATUS: U4.11 (PA06(AIN6/SER0:2/TC1:0))
D5_JACK_DETECT: U4.24 (PA15(XOUT/SER2:3+))
D9: U4.12 (PA07(AIN7/SER0:3/TC1:1))
EN: R48.2, U5.3 (EN)
GND: C4.2, C6.2, C20.2, C21.2, C22.2, C23.2, C24.1, C25.2, C33.2, C34.2, C35.2, J1.5 (GND), J1.6 (SHIELD), J1.7 (SHIELD), J1.8 (SHIELD), J1.9 (SHIELD), J1.10 (SHIELD), J1.11 (SHIELD), J1.S1 (SHIELD), J1.S2 (SHIELD), JP5.3 (GND), JP5.5 (GND), LED2.C, S1.1, S1.2 (1), U4.5 (GNDANA), U4.18 (GND), U4.35 (GND), U4.42 (GND), U5.2 (GND), U$5.P$5 (TP_GND), U$10.P2; also elsewhere on the board
HB_LED_D14: R1.1, U4.3 (PA02(AIN0/DAC))
INT_PIN_D6: U4.29 (PA20(SER5:2+))
LBO_PIN_A5: U4.47 (PB02(AIN10/SER5:0))
unnamed: LED2.A, R1.2
unnamed: C24.2, U4.1 (PA00(XIN32/SER1:0/TC2:0)), Y2.P$2 (2)
unnamed: C25.1, U4.2 (PA01(XOUT32/SER1:1/TC2:1)), Y2.P$1 (1)
OFF_PIN_D2: U4.23 (PA14(XIN/SER2:2+))
OUT: SJ6.2, U5.5 (OUT)
PGD_D7: U4.30 (PA21(SER5:3+))
READ_SPO2_A1: U4.7 (PB08(AIN2/SER4:0/TC4:0)); also elsewhere on the board
RX_LED: U4.48 (PB03(AIN11/SER5:1))
SCL: R29.1, U4.32 (PA23(I2C/SER3:0+)), U$10.P4
SCL_INT: U4.14 (PA09(I2C/AIN17/SER0:1+))
SDA: R28.1, U4.31 (PA22(I2C/SER3:0+)), U$10.P5
SDA_INT: U4.13 (PA08(I2C/AIN16/SER0:0+))
SPO2_CONNECTION_A2: U4.8 (PB09(AIN3/SER4:1/TC4:1)); also elsewhere on the board
SPO2_IR_D1: U4.15 (PA10(AIN18/SER0:2+))
SPO2_IR_D11: U4.25 (PA16(I2C/SER1:0+))
SPO2_IR_D13: U4.26 (PA17(I2C/SER1:1+))
SPO2_LED_D10: U4.27 (PA18(SER1:2+)); also elsewhere on the board
SPO2_RED_D0: U4.16 (PA11(AIN19/SER0:3+))
SPO2_RED_D12: U4.28 (PA19(SER1:3+))
STAT1_A3: U4.9 (PA04(AIN4/REFB/SER0:0/TC0:0))
STAT2_A4: U4.10 (PA05(AIN5/SER0:1/TC0:1))
SWCLK: JP5.4 (SWDCLK/TCK), U4.45 (PA30(SWCLK/SER1:2+)), U$5.P$3 (TP_SWCLK)
SWDIO: JP5.2 (SWDIO/TMS), U4.46 (PA31(SWDIO/SER1:3+)), U$5.P$2 (TP_SWDIO)
TX_LED: U4.39 (PA27)
USB_D_N: J1.2 (D-), U4.33 (PA24(SER3:2+))
USB_D_P: J1.3 (D+), U4.34 (PA25(SER3:3+))
USB_HOST_EN: U4.41 (PA28)
VBUS: C4.1, C34.1, C35.1, J1.1 (VCC), R48.1, SJ5.1, U5.1 (IN)
VDDANA: C22.1, L2.2, U4.6 (VDDANA)
VDDCORE: C21.1, U4.43 (VDDCORE)

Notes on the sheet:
PB22/23 are TXD/RXD to the EDBG
PB10/11 are MOSI/SCK to SPI header.
PA12 is SPI MISO (on SPI header).
PA13 is DGI GPIO0 (goes to EDBG).
PA5 is A4
PB2 is A5
ATSAMD21G
ATSAMD21G18 VDD Range: 1.62-3.63V
Cortex Debug/Program Connector
USB / Voltage Regulator
I2C Pull-Ups
Micro Controller
Headers etc
Reset
ToDo: - graceful shutdown after pressing Membrane - Testing SPI - Pi - Charge LED issue - LED's dimm issue - evt LTC2955 oid checken anders met XOR?
POWER AND FILTERING
Alleen voor Development:

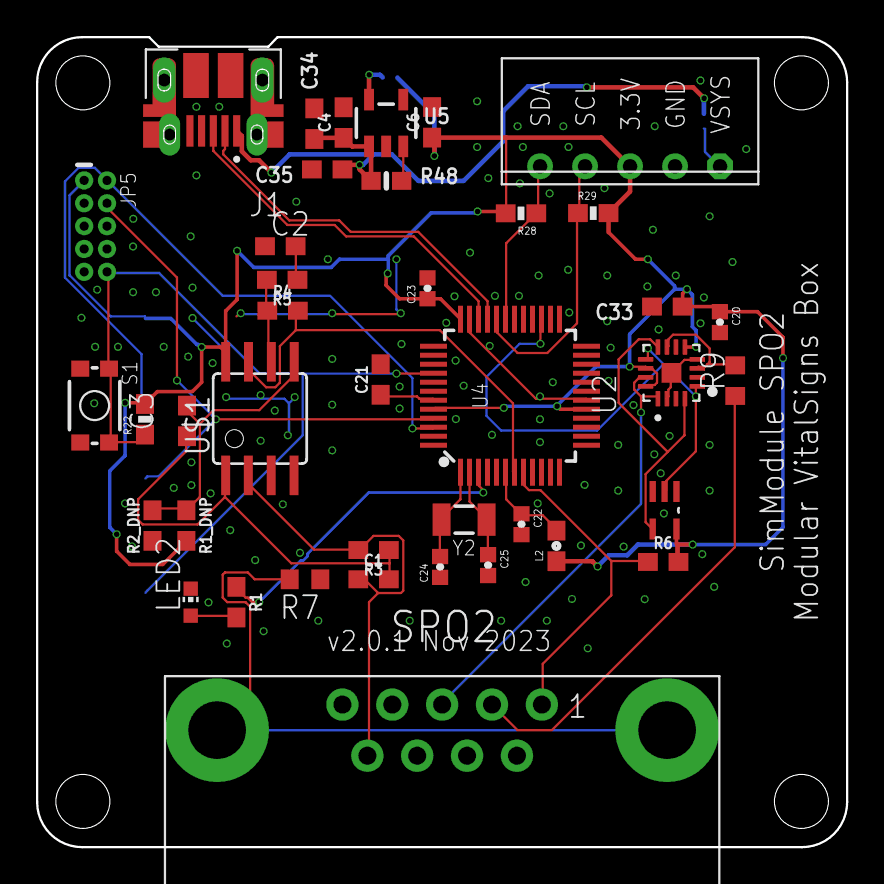
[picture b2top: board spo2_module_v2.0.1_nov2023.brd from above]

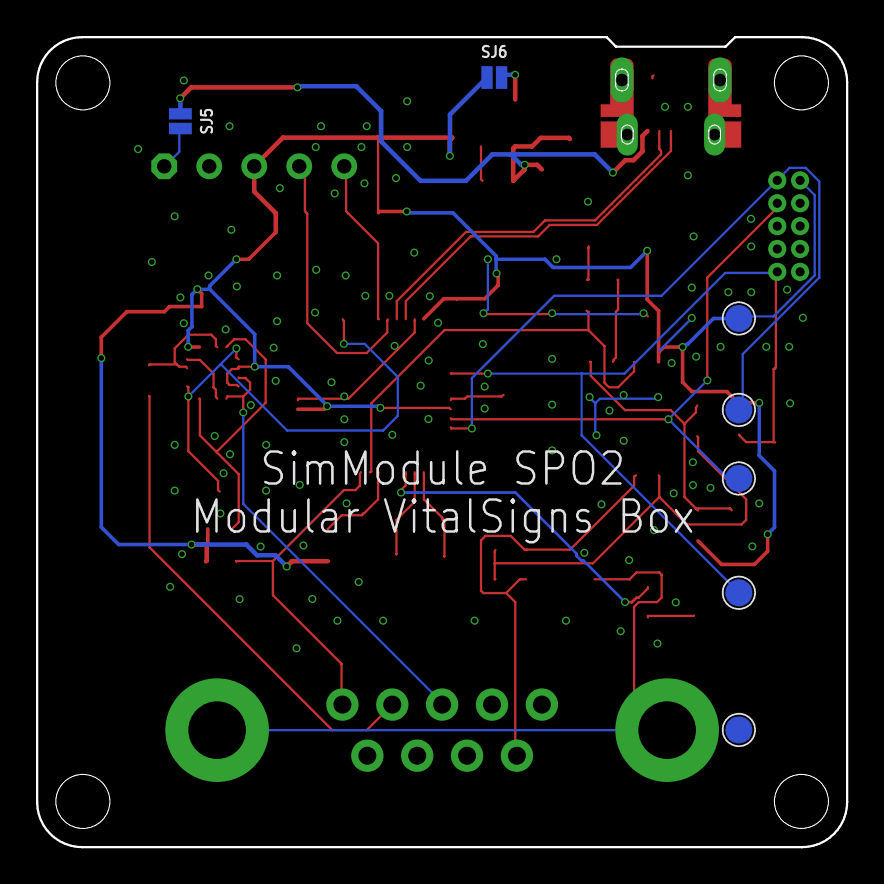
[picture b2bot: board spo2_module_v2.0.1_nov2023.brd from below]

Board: 2 copper layers, 45.0 x 45.0 mm, 44 parts (2 on the bottom side), 32 nets.

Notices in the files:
parts and their libraries:
microbuilder: This work is placed in the public domain, and may be freely used for commercial and non-commercial work with the following conditions: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
SparkFun-Resistors: Licensing: Creative Commons ShareAlike 4.0 International - https://creativecommons.org/licenses/by-sa/4.0
